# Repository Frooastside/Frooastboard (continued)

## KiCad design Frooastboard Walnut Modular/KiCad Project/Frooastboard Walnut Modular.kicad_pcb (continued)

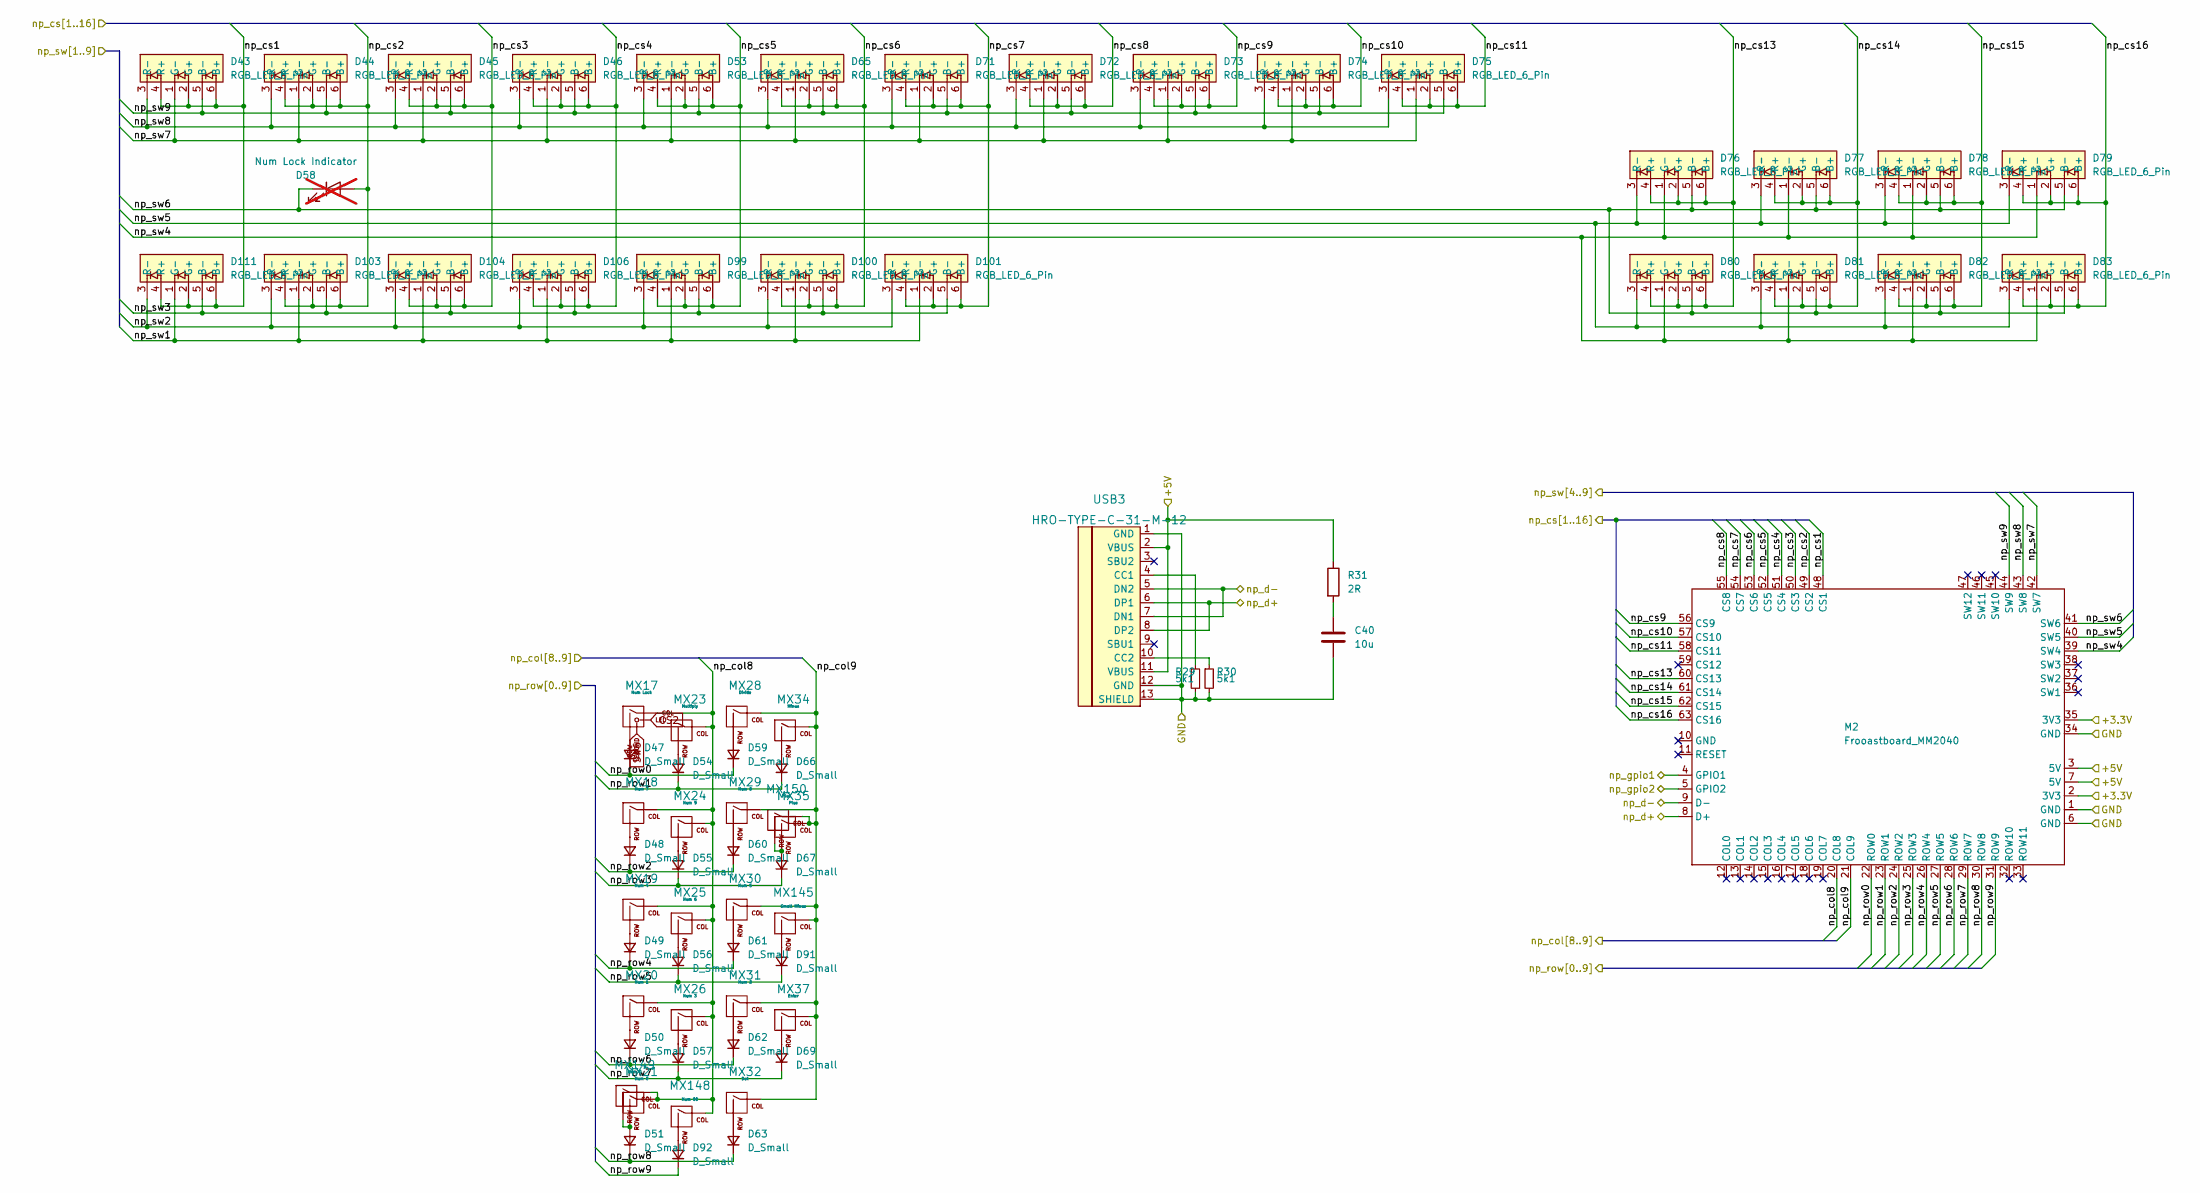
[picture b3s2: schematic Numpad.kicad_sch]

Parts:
C40: 10u; C_0805_2012Metric
D43, D44, D45, D46, D53, D65, D71, D72, D73, D74, D75, D76, D77, D78, D79, D80, D81, D82, D83, D99, D100, D101, D103, D104, D106, D111: RGB_LED_6_Pin; Everlight 99-235
D47, D48, D49, D50, D51, D54, D55, D56, D57, D59, D60, D61, D62, D63, D66, D67, D69, D91, D92: D_Small; D_0805_2012Metric
D58: Num Lock Indicator; LED_0805_2012Metric; not fitted
M2: Frooastboard_MM2040; MM2040
MX17: Num Lock; MXOnly-1U
MX18: Num 7; MXOnly-1U-NoLED
MX19: Num 4; MXOnly-1U-NoLED
MX20: Num 1; MXOnly-1U-NoLED
MX21: Num 0; MXOnly-2U-ReversedStabilizers-NoLED
MX23: Multiply; MXOnly-1U-NoLED
MX24: Num 9; MXOnly-1U-NoLED
MX25: Num 6; MXOnly-1U-NoLED
MX26: Num 3; MXOnly-1U-NoLED
MX28: Divide; MXOnly-1U-NoLED
MX29: Num 8; MXOnly-1U-NoLED
MX30: Num 5; MXOnly-1U-NoLED
MX31: Num 2; MXOnly-1U-NoLED
MX32: Dot; MXOnly-1U-NoLED
MX34: Minus; MXOnly-1U-NoLED
MX35: Plus; MXOnly-2U-NoLED
MX37: Enter; MXOnly-2U-ReversedVerticalStabilizers-NoLED
MX145: Small Minus; MXOnly-1U-NoLED
MX148: Num 00; MXOnly-1U-NoLED
MX149: Num 0; MXOnly-1U-NoLED
MX150: Plus; MXOnly-1U-NoLED
R29, R30: 5k1; R_0805_2012Metric
R31: 2R; R_0805_2012Metric
USB3: HRO-TYPE-C-31-M-12

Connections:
/Numpad/+3.3V: M2.2 (3V3), M2.35 (3V3)
/Numpad/+5V: M2.3 (5V), M2.7 (5V), R31.1, USB3.2 (VBUS), USB3.11 (VBUS); also elsewhere on the board
/Numpad/GND: C40.2, M2.1 (GND), M2.6 (GND), M2.34 (GND), R29.2, R30.2, USB3.1 (GND), USB3.12 (GND), USB3.13 (SHIELD); also elsewhere on the board
/Numpad/np_col8: M2.20 (COL8), MX17.1 (COL), MX18.1 (COL), MX19.1 (COL), MX20.1 (COL), MX21.1 (COL), MX23.1 (COL), MX24.1 (COL), MX25.1 (COL), MX26.1 (COL), MX148.1 (COL), MX149.1 (COL); also elsewhere on the board
/Numpad/np_col9: M2.21 (COL9), MX28.1 (COL), MX29.1 (COL), MX30.1 (COL), MX31.1 (COL), MX32.1 (COL), MX34.1 (COL), MX35.1 (COL), MX37.1 (COL), MX145.1 (COL), MX150.1 (COL); also elsewhere on the board
/Numpad/np_cs1: D43.2 (G+), D43.4 (R+), D43.6 (B+), D111.2 (G+), D111.4 (R+), D111.6 (B+), M2.48 (CS1); also elsewhere on the board
/Numpad/np_cs2: D44.2 (G+), D44.4 (R+), D44.6 (B+), D58.2 (A), D103.2 (G+), D103.4 (R+), D103.6 (B+), M2.49 (CS2); also elsewhere on the board
/Numpad/np_cs3: D45.2 (G+), D45.4 (R+), D45.6 (B+), D104.2 (G+), D104.4 (R+), D104.6 (B+), M2.50 (CS3); also elsewhere on the board
/Numpad/np_cs4: D46.2 (G+), D46.4 (R+), D46.6 (B+), D106.2 (G+), D106.4 (R+), D106.6 (B+), M2.51 (CS4); also elsewhere on the board
/Numpad/np_cs5: D53.2 (G+), D53.4 (R+), D53.6 (B+), D99.2 (G+), D99.4 (R+), D99.6 (B+), M2.52 (CS5); also elsewhere on the board
/Numpad/np_cs6: D65.2 (G+), D65.4 (R+), D65.6 (B+), D100.2 (G+), D100.4 (R+), D100.6 (B+), M2.53 (CS6); also elsewhere on the board
/Numpad/np_cs7: D71.2 (G+), D71.4 (R+), D71.6 (B+), D101.2 (G+), D101.4 (R+), D101.6 (B+), M2.54 (CS7); also elsewhere on the board
/Numpad/np_cs8: D72.2 (G+), D72.4 (R+), D72.6 (B+), M2.55 (CS8); also elsewhere on the board
/Numpad/np_cs9: D73.2 (G+), D73.4 (R+), D73.6 (B+), M2.56 (CS9); also elsewhere on the board
/Numpad/np_cs10: D74.2 (G+), D74.4 (R+), D74.6 (B+), M2.57 (CS10); also elsewhere on the board
/Numpad/np_cs11: D75.2 (G+), D75.4 (R+), D75.6 (B+), M2.58 (CS11); also elsewhere on the board
/Numpad/np_cs13: D76.2 (G+), D76.4 (R+), D76.6 (B+), D80.2 (G+), D80.4 (R+), D80.6 (B+), M2.60 (CS13); also elsewhere on the board
/Numpad/np_cs14: D77.2 (G+), D77.4 (R+), D77.6 (B+), D81.2 (G+), D81.4 (R+), D81.6 (B+), M2.61 (CS14); also elsewhere on the board
/Numpad/np_cs15: D78.2 (G+), D78.4 (R+), D78.6 (B+), D82.2 (G+), D82.4 (R+), D82.6 (B+), M2.62 (CS15); also elsewhere on the board
/Numpad/np_cs16: D79.2 (G+), D79.4 (R+), D79.6 (B+), D83.2 (G+), D83.4 (R+), D83.6 (B+), M2.63 (CS16); also elsewhere on the board
/Numpad/np_d+: M2.8 (D+), USB3.6 (DP1), USB3.8 (DP2)
/Numpad/np_d-: M2.9 (D-), USB3.5 (DN2), USB3.7 (DN1)
/Numpad/np_gpio1: M2.4 (GPIO1); also elsewhere on the board
/Numpad/np_gpio2: M2.5 (GPIO2); also elsewhere on the board
/Numpad/np_row0: D47.1 (K), D59.1 (K), M2.22 (ROW0); also elsewhere on the board
/Numpad/np_row1: D54.1 (K), D66.1 (K), M2.23 (ROW1); also elsewhere on the board
/Numpad/np_row2: D48.1 (K), D60.1 (K), M2.24 (ROW2); also elsewhere on the board
/Numpad/np_row3: D55.1 (K), D67.1 (K), M2.25 (ROW3); also elsewhere on the board
/Numpad/np_row4: D49.1 (K), D61.1 (K), M2.26 (ROW4); also elsewhere on the board
/Numpad/np_row5: D56.1 (K), D91.1 (K), M2.27 (ROW5); also elsewhere on the board
/Numpad/np_row6: D50.1 (K), D62.1 (K), M2.28 (ROW6); also elsewhere on the board
/Numpad/np_row7: D57.1 (K), D69.1 (K), M2.29 (ROW7); also elsewhere on the board
/Numpad/np_row8: D51.1 (K), D63.1 (K), M2.30 (ROW8); also elsewhere on the board
/Numpad/np_row9: D92.1 (K), M2.31 (ROW9); also elsewhere on the board
/Numpad/np_sw1: D99.1 (G-), D100.1 (G-), D101.1 (G-), D103.1 (G-), D104.1 (G-), D106.1 (G-), D111.1 (G-)
/Numpad/np_sw2: D99.3 (R-), D100.3 (R-), D101.3 (R-), D103.3 (R-), D104.3 (R-), D106.3 (R-), D111.3 (R-)
/Numpad/np_sw3: D99.5 (B-), D100.5 (B-), D101.5 (B-), D103.5 (B-), D104.5 (B-), D106.5 (B-), D111.5 (B-)
/Numpad/np_sw4: D76.1 (G-), D77.1 (G-), D78.1 (G-), D79.1 (G-), D80.1 (G-), D81.1 (G-), D82.1 (G-), D83.1 (G-), M2.39 (SW4); also elsewhere on the board
/Numpad/np_sw5: D76.3 (R-), D77.3 (R-), D78.3 (R-), D79.3 (R-), D80.3 (R-), D81.3 (R-), D82.3 (R-), D83.3 (R-), M2.40 (SW5); also elsewhere on the board
/Numpad/np_sw6: D58.1 (K), D76.5 (B-), D77.5 (B-), D78.5 (B-), D79.5 (B-), D80.5 (B-), D81.5 (B-), D82.5 (B-), D83.5 (B-), M2.41 (SW6); also elsewhere on the board
/Numpad/np_sw7: D43.1 (G-), D44.1 (G-), D45.1 (G-), D46.1 (G-), D53.1 (G-), D65.1 (G-), D71.1 (G-), D72.1 (G-), D73.1 (G-), D74.1 (G-), D75.1 (G-), M2.42 (SW7); also elsewhere on the board
/Numpad/np_sw8: D43.3 (R-), D44.3 (R-), D45.3 (R-), D46.3 (R-), D53.3 (R-), D65.3 (R-), D71.3 (R-), D72.3 (R-), D73.3 (R-), D74.3 (R-), D75.3 (R-), M2.43 (SW8); also elsewhere on the board
/Numpad/np_sw9: D43.5 (B-), D44.5 (B-), D45.5 (B-), D46.5 (B-), D53.5 (B-), D65.5 (B-), D71.5 (B-), D72.5 (B-), D73.5 (B-), D74.5 (B-), D75.5 (B-), M2.44 (SW9); also elsewhere on the board
CS2: MX17.3 (LED); also elsewhere on the board
unnamed: C40.1, R31.2
unnamed: D47.2 (A), MX17.2 (ROW)
unnamed: D48.2 (A), MX18.2 (ROW)
unnamed: D49.2 (A), MX19.2 (ROW)
unnamed: D50.2 (A), MX20.2 (ROW)
unnamed: D51.2 (A), MX21.2 (ROW), MX149.2 (ROW)
unnamed: D54.2 (A), MX23.2 (ROW)
unnamed: D55.2 (A), MX24.2 (ROW)
unnamed: D56.2 (A), MX25.2 (ROW)
unnamed: D57.2 (A), MX26.2 (ROW)
unnamed: D59.2 (A), MX28.2 (ROW)
unnamed: D60.2 (A), MX29.2 (ROW)
unnamed: D61.2 (A), MX30.2 (ROW)
unnamed: D62.2 (A), MX31.2 (ROW)
unnamed: D63.2 (A), MX32.2 (ROW)
unnamed: D66.2 (A), MX34.2 (ROW)
unnamed: D67.2 (A), MX35.2 (ROW), MX150.2 (ROW)
unnamed: D69.2 (A), MX37.2 (ROW)
unnamed: D91.2 (A), MX145.2 (ROW)
unnamed: D92.2 (A), MX148.2 (ROW)
unnamed: R29.1, USB3.4 (CC1)
unnamed: R30.1, USB3.10 (CC2)
SW6: MX17.4 (LEDGND)

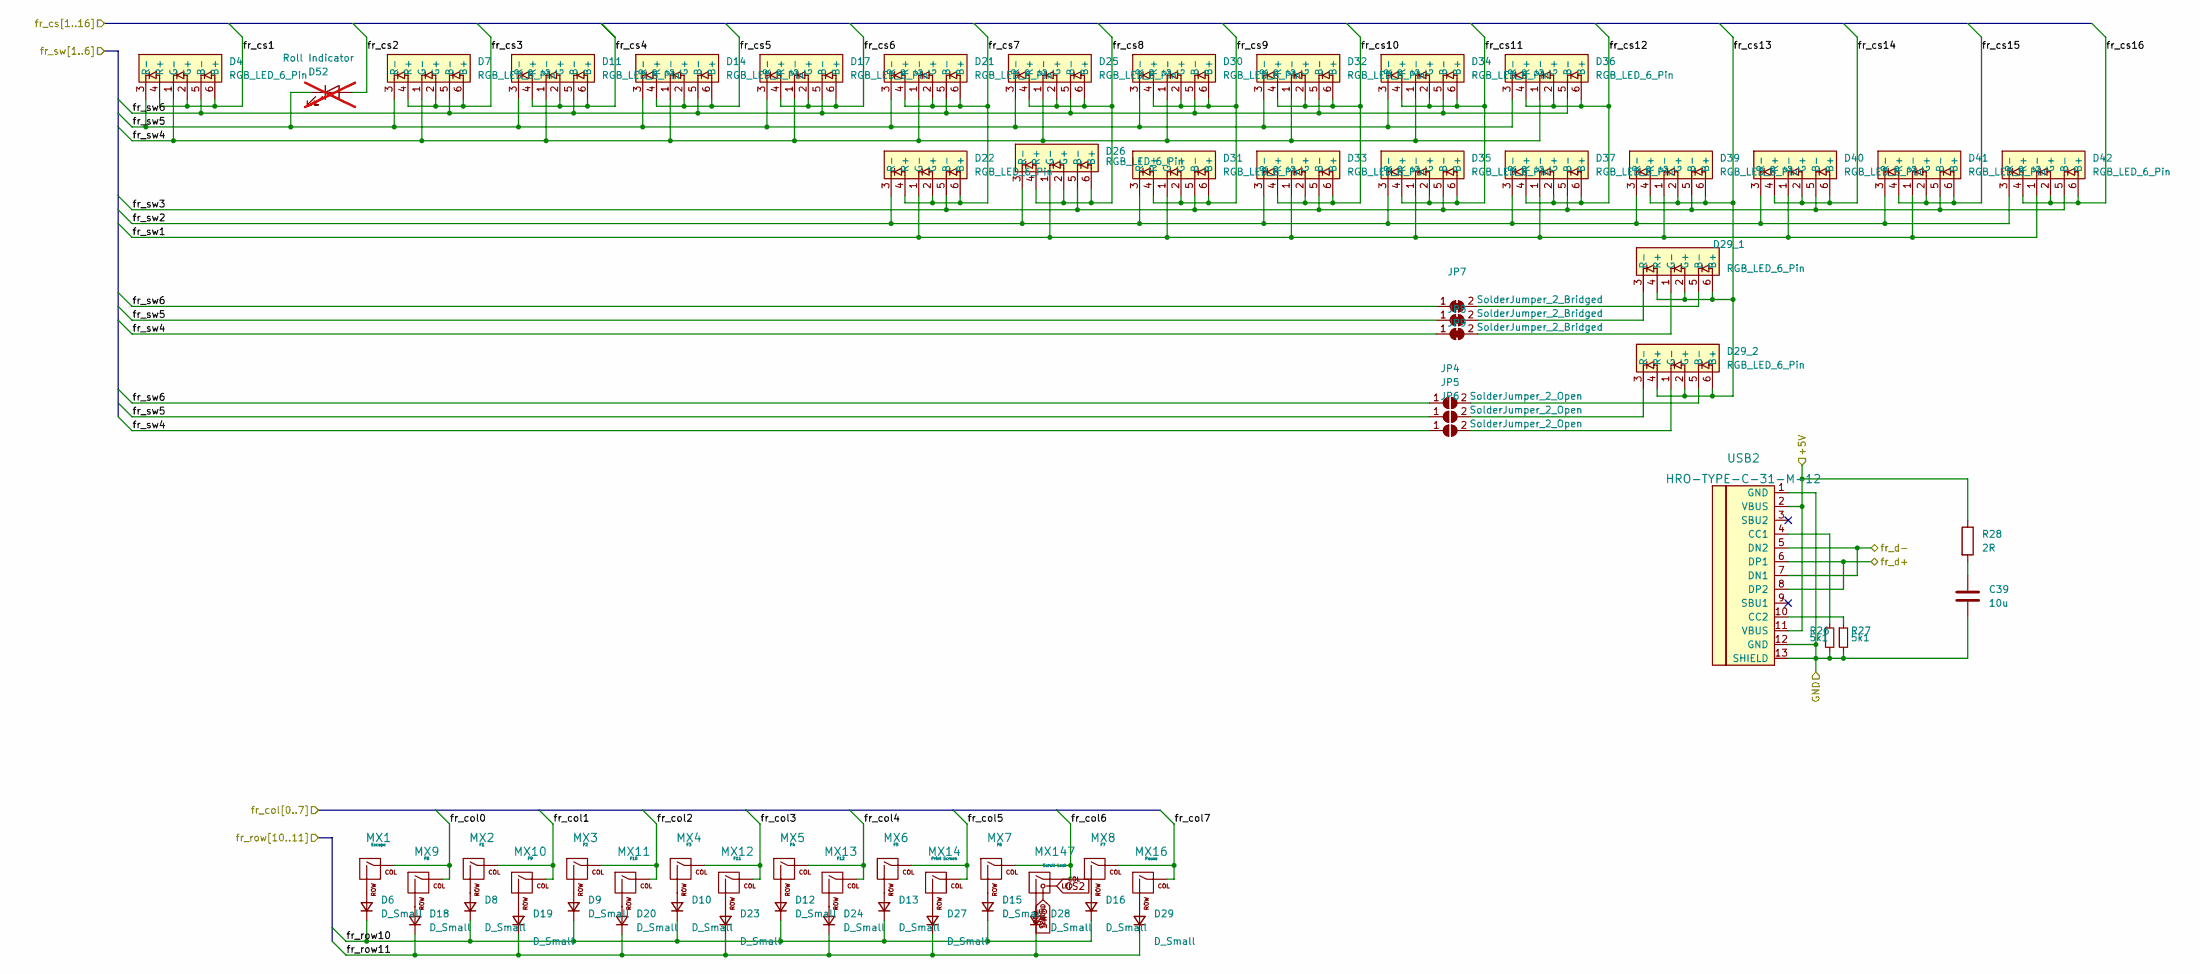
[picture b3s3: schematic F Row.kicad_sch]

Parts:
C39: 10u; C_0805_2012Metric
D4, D7, D11, D14, D17, D21, D22, D25, D26, D29_1, D29_2, D30, D31, D32, D33, D34, D35, D36, D37, D39, D40, D41, D42: RGB_LED_6_Pin; Everlight 99-235
D6, D8, D9, D10, D12, D13, D15, D16, D18, D19, D20, D23, D24, D27, D28, D29: D_Small; D_0805_2012Metric
D52: Roll Indicator; LED_0805_2012Metric; not fitted
JP4, JP5, JP6: SolderJumper_2_Open; SolderJumper-2_P1.3mm_Open_RoundedPad1.0x1.5mm
JP7, JP8, JP9: SolderJumper_2_Bridged; SolderJumper-2_P1.3mm_Bridged_RoundedPad1.0x1.5mm
MX1: Escape; MXOnly-1U-NoLED
MX2: F1; MXOnly-1U-NoLED
MX3: F2; MXOnly-1U-NoLED
MX4: F3; MXOnly-1U-NoLED
MX5: F4; MXOnly-1U-NoLED
MX6: F5; MXOnly-1U-NoLED
MX7: F6; MXOnly-1U-NoLED
MX8: F7; MXOnly-1U-NoLED
MX9: F8; MXOnly-1U-NoLED
MX10: F9; MXOnly-1U-NoLED
MX11: F10; MXOnly-1U-NoLED
MX12: F11; MXOnly-1U-NoLED
MX13: F12; MXOnly-1U-NoLED
MX14: Print Screen; MXOnly-1U-NoLED
MX16: Pause; MXOnly-1U-NoLED
MX147: Scroll Lock; MXOnly-1U
R26, R27: 5k1; R_0805_2012Metric
R28: 2R; R_0805_2012Metric
USB2: HRO-TYPE-C-31-M-12

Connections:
/F Row/+5V: R28.1, USB2.2 (VBUS), USB2.11 (VBUS); also elsewhere on the board
/F Row/GND: C39.2, R26.2, R27.2, USB2.1 (GND), USB2.12 (GND), USB2.13 (SHIELD); also elsewhere on the board
/F Row/fr_col0: MX1.1 (COL), MX9.1 (COL); also elsewhere on the board
/F Row/fr_col1: MX2.1 (COL), MX10.1 (COL); also elsewhere on the board
/F Row/fr_col2: MX3.1 (COL), MX11.1 (COL); also elsewhere on the board
/F Row/fr_col3: MX4.1 (COL), MX12.1 (COL); also elsewhere on the board
/F Row/fr_col4: MX5.1 (COL), MX13.1 (COL); also elsewhere on the board
/F Row/fr_col5: MX6.1 (COL), MX14.1 (COL); also elsewhere on the board
/F Row/fr_col6: MX7.1 (COL), MX147.1 (COL); also elsewhere on the board
/F Row/fr_col7: MX8.1 (COL), MX16.1 (COL); also elsewhere on the board
/F Row/fr_cs1: D4.2 (G+), D4.4 (R+), D4.6 (B+); also elsewhere on the board
/F Row/fr_cs3: D7.2 (G+), D7.4 (R+), D7.6 (B+); also elsewhere on the board
/F Row/fr_cs4: D11.2 (G+), D11.4 (R+), D11.6 (B+); also elsewhere on the board
/F Row/fr_cs5: D14.2 (G+), D14.4 (R+), D14.6 (B+); also elsewhere on the board
/F Row/fr_cs6: D17.2 (G+), D17.4 (R+), D17.6 (B+); also elsewhere on the board
/F Row/fr_cs7: D21.2 (G+), D21.4 (R+), D21.6 (B+), D22.2 (G+), D22.4 (R+), D22.6 (B+); also elsewhere on the board
/F Row/fr_cs8: D25.2 (G+), D25.4 (R+), D25.6 (B+), D26.2 (G+), D26.4 (R+), D26.6 (B+); also elsewhere on the board
/F Row/fr_cs9: D30.2 (G+), D30.4 (R+), D30.6 (B+), D31.2 (G+), D31.4 (R+), D31.6 (B+); also elsewhere on the board
/F Row/fr_cs10: D32.2 (G+), D32.4 (R+), D32.6 (B+), D33.2 (G+), D33.4 (R+), D33.6 (B+); also elsewhere on the board
/F Row/fr_cs11: D34.2 (G+), D34.4 (R+), D34.6 (B+), D35.2 (G+), D35.4 (R+), D35.6 (B+); also elsewhere on the board
/F Row/fr_cs12: D36.2 (G+), D36.4 (R+), D36.6 (B+), D37.2 (G+), D37.4 (R+), D37.6 (B+); also elsewhere on the board
/F Row/fr_cs13: D29_1.2 (G+), D29_1.4 (R+), D29_1.6 (B+), D29_2.2 (G+), D29_2.4 (R+), D29_2.6 (B+), D39.2 (G+), D39.4 (R+), D39.6 (B+); also elsewhere on the board
/F Row/fr_cs14: D40.2 (G+), D40.4 (R+), D40.6 (B+); also elsewhere on the board
/F Row/fr_cs15: D41.2 (G+), D41.4 (R+), D41.6 (B+); also elsewhere on the board
/F Row/fr_cs16: D42.2 (G+), D42.4 (R+), D42.6 (B+); also elsewhere on the board
/F Row/fr_d+: USB2.6 (DP1), USB2.8 (DP2); also elsewhere on the board
/F Row/fr_d-: USB2.5 (DN2), USB2.7 (DN1); also elsewhere on the board
/F Row/fr_row10: D6.1 (K), D8.1 (K), D9.1 (K), D10.1 (K), D12.1 (K), D13.1 (K), D15.1 (K), D16.1 (K); also elsewhere on the board
/F Row/fr_row11: D18.1 (K), D19.1 (K), D20.1 (K), D23.1 (K), D24.1 (K), D27.1 (K), D28.1 (K), D29.1 (K); also elsewhere on the board
/F Row/fr_sw1: D22.1 (G-), D26.1 (G-), D31.1 (G-), D33.1 (G-), D35.1 (G-), D37.1 (G-), D39.1 (G-), D40.1 (G-), D41.1 (G-), D42.1 (G-); also elsewhere on the board
/F Row/fr_sw2: D22.3 (R-), D26.3 (R-), D31.3 (R-), D33.3 (R-), D35.3 (R-), D37.3 (R-), D39.3 (R-), D40.3 (R-), D41.3 (R-), D42.3 (R-); also elsewhere on the board
/F Row/fr_sw3: D22.5 (B-), D26.5 (B-), D31.5 (B-), D33.5 (B-), D35.5 (B-), D37.5 (B-), D39.5 (B-), D40.5 (B-), D41.5 (B-), D42.5 (B-); also elsewhere on the board
CS2: MX147.3 (LED); also elsewhere on the board
unnamed: C39.1, R28.2
unnamed: D6.2 (A), MX1.2 (ROW)
unnamed: D8.2 (A), MX2.2 (ROW)
unnamed: D9.2 (A), MX3.2 (ROW)
unnamed: D10.2 (A), MX4.2 (ROW)
unnamed: D12.2 (A), MX5.2 (ROW)
unnamed: D13.2 (A), MX6.2 (ROW)
unnamed: D15.2 (A), MX7.2 (ROW)
unnamed: D16.2 (A), MX8.2 (ROW)
unnamed: D18.2 (A), MX9.2 (ROW)
unnamed: D19.2 (A), MX10.2 (ROW)
unnamed: D20.2 (A), MX11.2 (ROW)
unnamed: D23.2 (A), MX12.2 (ROW)
unnamed: D24.2 (A), MX13.2 (ROW)
unnamed: D27.2 (A), MX14.2 (ROW)
unnamed: D28.2 (A), MX147.2 (ROW)
unnamed: D29.2 (A), MX16.2 (ROW)
unnamed: R26.1, USB2.4 (CC1)
unnamed: R27.1, USB2.10 (CC2)
SW5: MX147.4 (LEDGND)
